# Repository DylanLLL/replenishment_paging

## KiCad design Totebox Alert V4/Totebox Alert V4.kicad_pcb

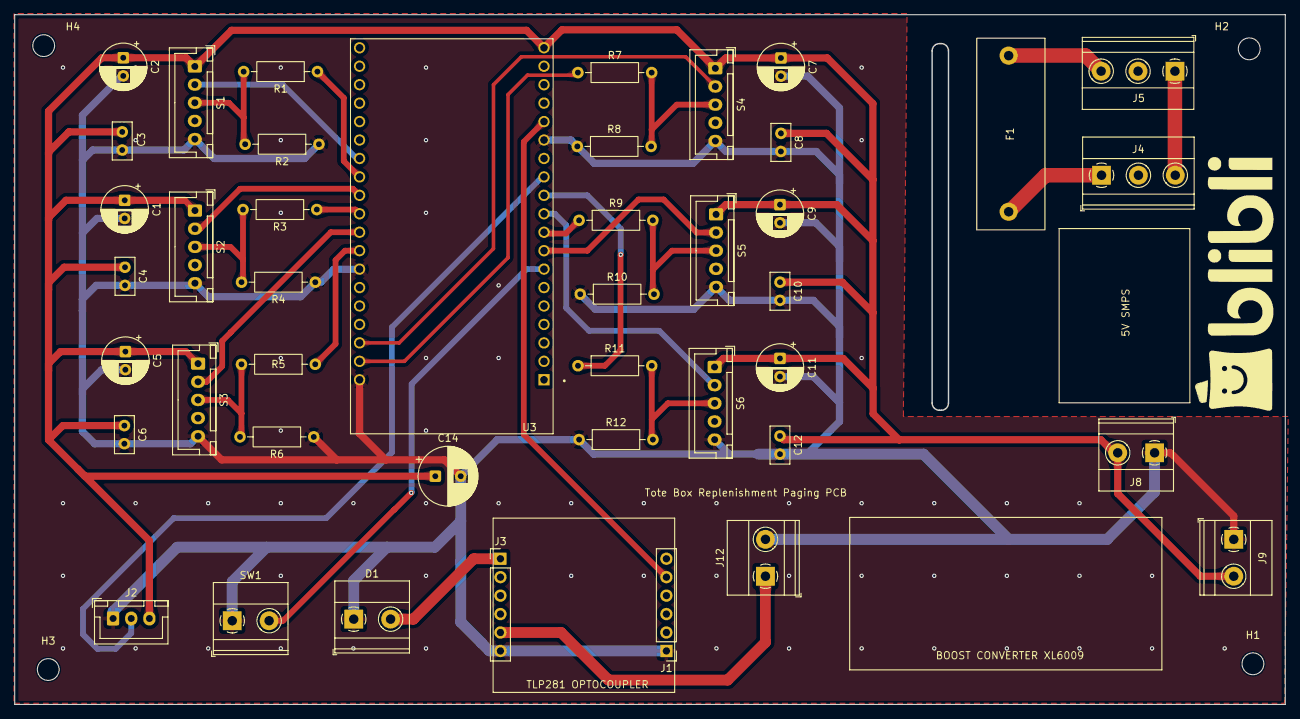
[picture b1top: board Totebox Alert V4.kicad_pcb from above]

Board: 2 copper layers, 174.8 x 94.9 mm, 47 parts (0 on the bottom side), 28 nets.

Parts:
C1, C2, C5, C7, C9, C11: 100u; CP_Radial_D6.3mm_P2.50mm
C3, C4, C6, C8, C10, C12: 0.1u; C_Disc_D5.0mm_W2.5mm_P2.50mm
C14: 470u; CP_Radial_D8.0mm_P3.50mm
D1: LED; TerminalBlock_Phoenix_MKDS-1,5-2-5.08_1x02_P5.08mm_Horizont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
F1: Fuse_Small; Fuseholder_5x20_THROUGH_HOLE_custom
H1, H2, H3, H4: MountingHole_3mm
J1: Optocoupler In; PinHeader_1x06_P2.54mm_Vertical
J2: Buzzer; JST_XH_B3B-XH-A_1x03_P2.50mm_Vertical
J3: Optocoupler Out; PinHeader_1x06_P2.54mm_Vertical
J4: SMPS IN; TerminalBlock_Phoenix_MKDS-1,5-3-5.08_1x03_P5.08mm_Horizont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
J5: AC; TerminalBlock_Phoenix_MKDS-1,5-3-5.08_1x03_P5.08mm_Horizont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
J8: SMPS OUT; TerminalBlock_Phoenix_MKDS-1,5-2-5.08_1x02_P5.08mm_Horizont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
J9: Boost Conv. In; TerminalBlock_Phoenix_MKDS-1,5-2-5.08_1x02_P5.08mm_Horizont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
J12: Boost Conv. Out; TerminalBlock_Phoenix_MKDS-1,5-2-5.08_1x02_P5.08mm_Horizont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
R1, R3, R5, R7, R9, R11: 1k; R_Axial_DIN0207_L6.3mm_D2.5mm_P10.16mm_Horizontal
R2, R4, R6, R8, R10, R12: 2k; R_Axial_DIN0207_L6.3mm_D2.5mm_P10.16mm_Horizontal
S1, S2, S3, S4, S5, S6: HY-SRF05; JST_XH_B5B-XH-A_1x05_P2.50mm_Vertical
SW1: SW_SPST; TerminalBlock_Phoenix_MKDS-1,5-2-5.08_1x02_P5.08mm_Horizont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
U3: ESP32-DEVKITC-32UE; ESPRESSIF_ESP32-DEVKITC-32UE

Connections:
5V: C1.1, C2.1, C3.1, C4.1, C5.1, C6.1, C7.1, C8.1, C9.1, C10.1, C11.1, C12.1, C14.1, J2.3, J8.2 (VOUT+), J9.2 (5V+), S1.1 (VCC), S2.1 (VCC), S3.1 (VCC), S4.1 (VCC), S5.1 (VCC), S6.1 (VCC), U3.19 (5V)
12V: J3.5 (HVCC), J12.1 (12V+)
ECHO1: R1.1, U3.31 (16)
ECHO2: R3.1, U3.29 (5)
ECHO3: R5.1, U3.27 (19)
ECHO4: R7.1, U3.21 (23)
ECHO5: R9.1, U3.9 (25)
ECHO6: R11.1, U3.11 (27)
GND: C1.2, C2.2, C3.2, C4.2, C5.2, C6.2, C7.2, C8.2, C9.2, C10.2, C11.2, C12.2, C14.2, D1.1 (K), J1.1 (GND), J2.1, J3.6 (HGND), J8.1 (VOUT-), J9.1 (5V-), J12.2 (12V-), R2.1, R4.1, R6.1, R8.1, R10.1, R12.1, S1.5 (GND), S2.5 (GND), S3.5 (GND), S4.5 (GND), S5.5 (GND), S6.5 (GND), SW1.1 (A), U3.14 (GND), U3.20 (GND), U3.26 (GND)
NO: SW1.2 (B), U3.7 (32)
unnamed: D1.2 (A), J3.1 (OUT1)
unnamed: J2.2, U3.12 (14)
unnamed: F1.2, J4.1
unnamed: J4.3, J5.1
unnamed: F1.1, J5.3
unnamed: R1.2, R2.2, S1.3 (ECHO)
unnamed: R3.2, R4.2, S2.3 (ECHO)
unnamed: R5.2, R6.2, S3.3 (ECHO)
unnamed: R7.2, R8.2, S4.3 (ECHO)
unnamed: R9.2, R10.2, S5.3 (ECHO)
unnamed: R11.2, R12.2, S6.3 (ECHO)
OPTO_IN1: J1.5 (IN1), U3.15 (13)
TRIG1: S1.2 (TRIG), U3.32 (4)
TRIG2: S2.2 (TRIG), U3.30 (17)
TRIG3: S3.2 (TRIG), U3.28 (18)
TRIG4: S4.2 (TRIG), U3.22
TRIG5: S5.2 (TRIG), U3.8 (33)
TRIG6: S6.2 (TRIG), U3.10 (26)

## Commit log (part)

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2026-04-24 if only 4 out of 6 sensors detected, allert turns off. Ground button unit can reset and give clear alert
2026-04-27 add LED blinking if wifi is not connected
2026-05-29 remove ground floor button functionalities
2026-06-19 add floor unit PCB version 1 2 3
